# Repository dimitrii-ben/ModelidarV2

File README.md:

# ModéLiDAR II-Projet 1A 2023
> Reprise du projet ModéLiDAR fait en 2022 par des étudiants de l'ENSEA en 1ere année.

L’objectif de ce projet est de contrôler un robot capable de faire de la reconnaissance de différents environnements grâce à un LiDAR intégré.

## Matériels utilisés
- le châssis d’une voiture RC équipé d’une batterie et de quatre moteurs et d'une caméra,
- 1 LiDAR (Velodyne Puck-Hi-Res),
- 1 Raspberry Pi 4,
- 1 STM32 (STM32F446),
- 1 joystick,
- plusieurs cartes PCB réalisés par le groupe précédent

## Description du dépôt Git
Dans ce dépôt Git vous trouverez ;
- les fichiers KiCad de la PCB servant à alimenter les moteurs droits et gauches,
- le code à implémenter sur la STM32 afin de générer les PWM pour les moteurs,
- et le code permettant une commande à distance du ModéLiDAR à l'aide d'un joystick, il est composé de 3 noeuds
  - un nœud dédié au joystick (joy_node),
  - un nœud de communication avec la Raspberry Pi (communication_node),
  - et un nœud de traitement et envoi des commandes à la STM32 (stm32_node)

## Etudiants en charge du projet :
- BAZAIA Tancrède,
- BENOIT Dimitrii,
- CHENDEA Anton,
- FERRERI Pierre,
- GAMIETTE David,
- PETIT Alexandre

## Professeurs encadrants le projet :
- BARES Christophe,
- MARTIN Alexis

Plus d'informations dans le [rapport de projet](https://docs.google.com/document/d/1G-ZUsXAikZ85jQwoOplvorRcLATqSPql3EAao3XSJj0)

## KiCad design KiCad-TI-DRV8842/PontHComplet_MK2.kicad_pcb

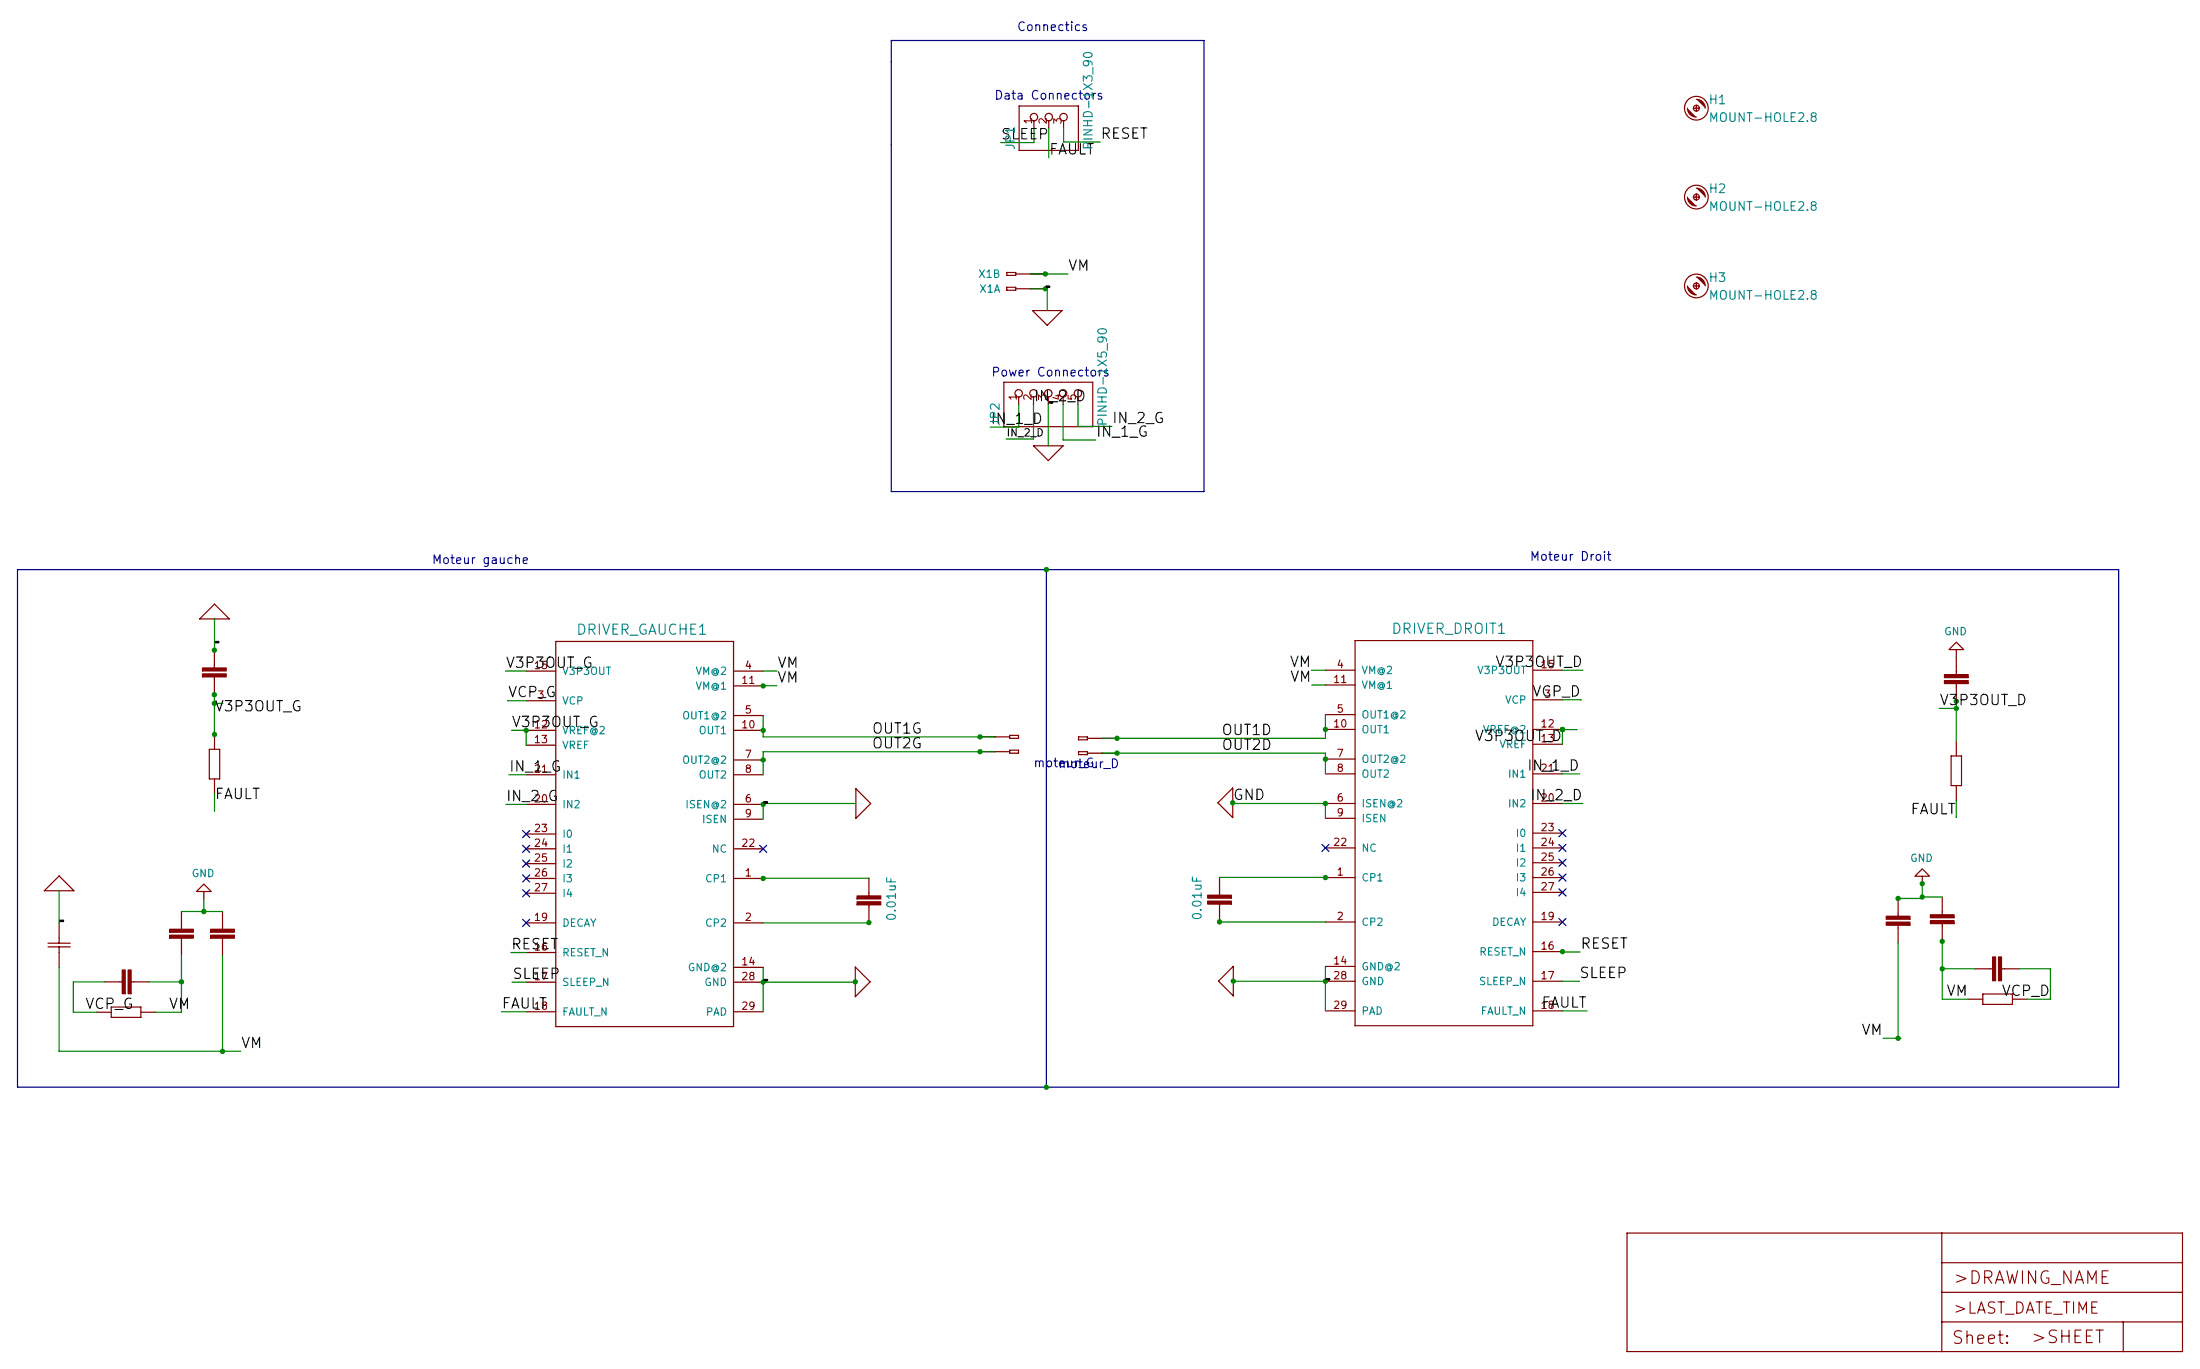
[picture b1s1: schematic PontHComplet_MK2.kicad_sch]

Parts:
D1, D2, D3: 0.1uF; C1206K
D4: 1M; R1206W
D5: 10K; R1206W
D8: 0.47uF; C1206K
D10: 0.01uF; C1206K
DRIVER_DROIT1: DRV8842PWPRPWP0028C_M; PWP0028C_M
DRIVER_GAUCHE1: DRV8842PWPRPWP0028C_M; PWP0028C_M
G1, G2, G4: 0.1uF; C1206K
G3: 220uF; CAP_60557008_WRE-M
G5: 1M; R1206W
G6: 10K; R1206W
G8: 0.47uF; C1206K
G11: 0.01uF; C1206K
H1, H2, H3: MOUNT-HOLE2.8; 2,8
JP1: PINHD-1X3_90; 1X03_90
JP2: PINHD-1X5_90; 1X05_90
MOTEUR_D1: WAGO2-255-402-508; 255-402-508
MOTEUR_G1: WAGO2-255-402-508; 255-402-508
X1: WAGO2-255-402-508; 255-402-508

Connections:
0: D1.1, D2.1, D8.1, DRIVER_DROIT1.6 (ISEN@2), DRIVER_DROIT1.9 (ISEN), DRIVER_DROIT1.14 (GND@2), DRIVER_DROIT1.28 (GND), DRIVER_DROIT1.29 (PAD), DRIVER_DROIT1.V, DRIVER_GAUCHE1.6 (ISEN@2), DRIVER_GAUCHE1.9 (ISEN), DRIVER_GAUCHE1.14 (GND@2), DRIVER_GAUCHE1.28 (GND), DRIVER_GAUCHE1.29 (PAD), DRIVER_GAUCHE1.V, G1.1, G2.1, G3.1, G8.1, JP2.3, X1.A1, X1.B1
/FAULT: D5.1, DRIVER_DROIT1.18 (FAULT_N), DRIVER_GAUCHE1.18 (FAULT_N), G6.1, JP1.2
/IN_1_D: DRIVER_DROIT1.21 (IN1), JP2.1
/IN_1_G: DRIVER_GAUCHE1.21 (IN1), JP2.4
/IN_2_D: DRIVER_DROIT1.20 (IN2), JP2.2
/IN_2_G: DRIVER_GAUCHE1.20 (IN2), JP2.5
/OUT1D: DRIVER_DROIT1.5 (OUT1@2), DRIVER_DROIT1.10 (OUT1), MOTEUR_D1.A2 (A1), MOTEUR_D1.B2 (B1)
/OUT1G: DRIVER_GAUCHE1.5 (OUT1@2), DRIVER_GAUCHE1.10 (OUT1), MOTEUR_G1.A1, MOTEUR_G1.B1
/OUT2D: DRIVER_DROIT1.7 (OUT2@2), DRIVER_DROIT1.8 (OUT2), MOTEUR_D1.A1, MOTEUR_D1.B1
/OUT2G: DRIVER_GAUCHE1.7 (OUT2@2), DRIVER_GAUCHE1.8 (OUT2), MOTEUR_G1.A2 (A1), MOTEUR_G1.B2 (B1)
/RESET: DRIVER_DROIT1.16 (RESET_N), DRIVER_GAUCHE1.16 (RESET_N), JP1.3
/SLEEP: DRIVER_DROIT1.17 (SLEEP_N), DRIVER_GAUCHE1.17 (SLEEP_N), JP1.1
/V3P3OUT_D: D5.2, D8.2, DRIVER_DROIT1.12 (VREF@2), DRIVER_DROIT1.13 (VREF), DRIVER_DROIT1.15 (V3P3OUT)
/V3P3OUT_G: DRIVER_GAUCHE1.12 (VREF@2), DRIVER_GAUCHE1.13 (VREF), DRIVER_GAUCHE1.15 (V3P3OUT), G6.2, G8.2
/VCP_D: D3.1, D4.1, DRIVER_DROIT1.3 (VCP)
/VCP_G: DRIVER_GAUCHE1.3 (VCP), G4.1, G5.1
/VM: D1.2, D2.2, D3.2, D4.2, DRIVER_DROIT1.4 (VM@2), DRIVER_DROIT1.11 (VM@1), DRIVER_GAUCHE1.4 (VM@2), DRIVER_GAUCHE1.11 (VM@1), G1.2, G2.2, G3.2, G4.2, G5.2, X1.A2 (A1), X1.B2 (B1)
unnamed: D10.1, DRIVER_DROIT1.1 (CP1)
unnamed: D10.2, DRIVER_DROIT1.2 (CP2)
unnamed: DRIVER_GAUCHE1.1 (CP1), G11.1
unnamed: DRIVER_GAUCHE1.2 (CP2), G11.2

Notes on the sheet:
Moteur gauche
Connectics
Moteur Droit
Data Connectors
Power Connectors
moteur_G
moteur_D

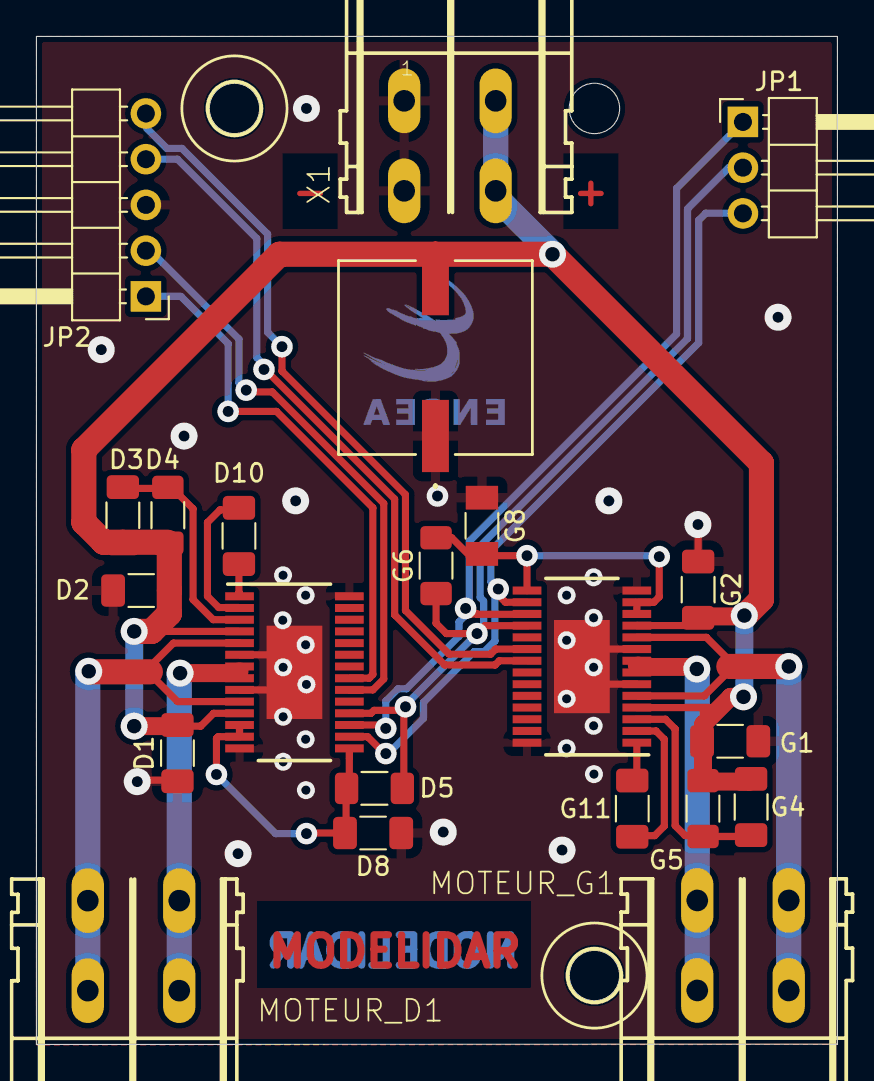
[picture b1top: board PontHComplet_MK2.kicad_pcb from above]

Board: 2 copper layers, 44.5 x 56.0 mm, 25 parts (1 on the bottom side), 21 nets.

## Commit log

2023-05-11 ajout de "KiCad-TI-DRV8842"
2023-05-11 ajout de "ModeLIDARv2-STM-1"
    fichiers pour la NUCLEO F446RE
2023-06-08 ajout du code du joystick
